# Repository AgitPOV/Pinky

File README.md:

Pinky
=====

Agit P.O.V. Pinky 2

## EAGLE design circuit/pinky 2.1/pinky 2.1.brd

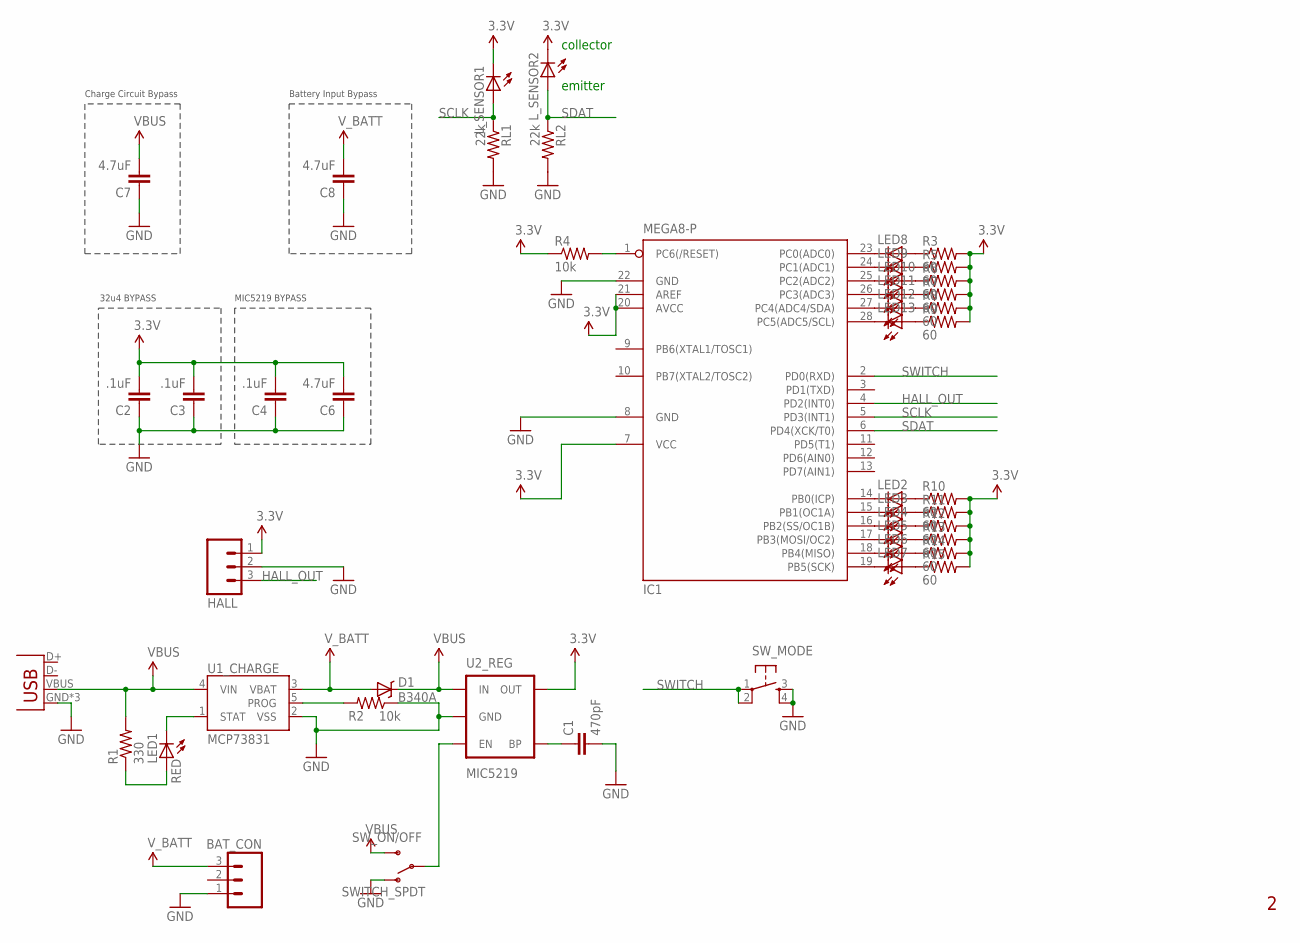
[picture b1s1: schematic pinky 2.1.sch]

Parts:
BAT_CON: M03PTH; 1X03
C1: 470pF; 1206
C2, C3, C4: .1uF; 1206
C6, C7, C8: 4.7uF; 1206
D1: B340A; SMA-DIODE
HALL: M03PTH; 1X03
IC1: MEGA8-P; DIL28-3
LED1: RED; LED-1206
LED2, LED3, LED4, LED5, LED6, LED7, LED8, LED9, LED10, LED11, LED12, LED13: LED1206; LED-1206
L_SENSOR1, L_SENSOR2: LED3MM
R1: 330; 1206
R2, R4: 10k; 1206
R3, R5, R6, R7, R8, R9, R10, R11, R12, R13, R14, R15: 60; 1206
RL1, RL2: 22k; 1206
SW_MODE: TAC_SWITCHPTH; TACTILE-PTH
SW_ON/OFF: SWITCH_SPDT; KPS-1290
U1_CHARGE: MCP73831; SOT23-5
U2_REG: MIC5219; SOT23-5
X1_USB_MICRO: USB-MICROB

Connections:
3.3V: C2.2, C3.2, C4.2, C6.2, HALL.1, IC1.7 (VCC), IC1.20 (AVCC), IC1.21 (AREF), L_SENSOR1.K (C), L_SENSOR2.K (C), R3.2, R4.1, R5.2, R6.2, R7.2, R8.2, R9.2, R10.2, R11.2, R12.2, R13.2, R14.2, R15.2, U2_REG.5 (OUT)
5V: C7.2, D1.C, R1.2, SW_ON/OFF.S, U1_CHARGE.4 (VIN), U2_REG.1 (IN), X1_USB_MICRO.VBUS
GND: BAT_CON.1, C1.2, C2.1, C3.1, C4.1, C6.1, C7.1, C8.1, HALL.2, IC1.8 (GND), IC1.22 (GND), R2.1, RL1.2, RL2.2, SW_MODE.3, SW_MODE.4, SW_ON/OFF.O, U1_CHARGE.2 (VSS), U2_REG.2 (GND), X1_USB_MICRO.GND, X1_USB_MICRO.MT1 (GND), X1_USB_MICRO.MT2 (GND)
HALL_OUT: HALL.3, IC1.4 (PD2(INT0))
unnamed: IC1.1 (PC6(/RESET)), R4.2
unnamed: SW_ON/OFF.P, U2_REG.3 (EN)
unnamed: LED1.A, R1.1
unnamed: LED1.C, U1_CHARGE.1 (STAT)
unnamed: IC1.14 (PB0(ICP)), LED2.C
unnamed: R2.2, U1_CHARGE.5 (PROG)
unnamed: IC1.15 (PB1(OC1A)), LED3.C
unnamed: C1.1, U2_REG.4 (BP)
unnamed: IC1.16 (PB2(SS/OC1B)), LED4.C
unnamed: IC1.17 (PB3(MOSI/OC2)), LED5.C
unnamed: IC1.18 (PB4(MISO)), LED6.C
unnamed: IC1.19 (PB5(SCK)), LED7.C
unnamed: IC1.23 (PC0(ADC0)), LED8.C
unnamed: IC1.24 (PC1(ADC1)), LED9.C
unnamed: IC1.25 (PC2(ADC2)), LED10.C
unnamed: IC1.26 (PC3(ADC3)), LED11.C
unnamed: IC1.27 (PC4(ADC4/SDA)), LED12.C
unnamed: IC1.28 (PC5(ADC5/SCL)), LED13.C
unnamed: LED8.A, R3.1
unnamed: LED9.A, R5.1
unnamed: LED10.A, R6.1
unnamed: LED11.A, R7.1
unnamed: LED12.A, R8.1
unnamed: LED13.A, R9.1
unnamed: LED2.A, R10.1
unnamed: LED3.A, R11.1
unnamed: LED4.A, R12.1
unnamed: LED5.A, R13.1
unnamed: LED6.A, R14.1
unnamed: LED7.A, R15.1
SCLK: IC1.5 (PD3(INT1)), L_SENSOR1.A, RL1.1
SDAT: IC1.6 (PD4(XCK/T0)), L_SENSOR2.A, RL2.1
SWITCH: IC1.2 (PD0(RXD)), SW_MODE.1, SW_MODE.2
V_BATT: BAT_CON.3, C8.2, D1.A, U1_CHARGE.3 (VBAT)

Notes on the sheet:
32u4 BYPASS
MIC5219 BYPASS
Charge Circuit Bypass
Battery Input Bypass
collector
emitter

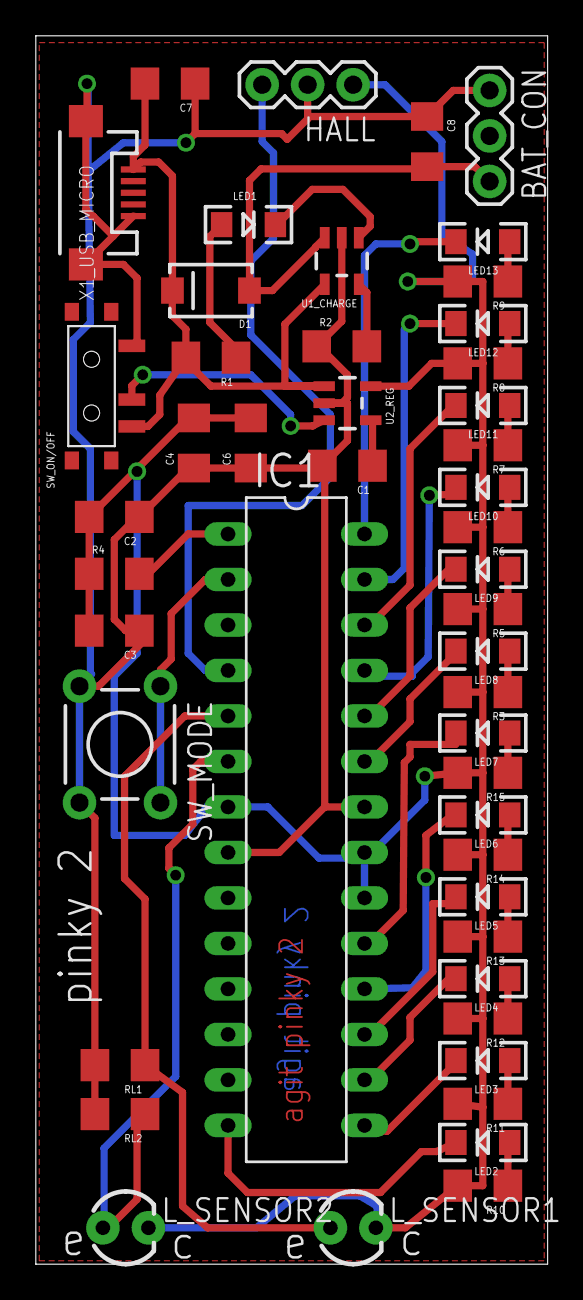
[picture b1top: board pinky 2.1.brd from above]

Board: 2 copper layers, 28.6 x 68.6 mm, 48 parts (0 on the bottom side), 38 nets.

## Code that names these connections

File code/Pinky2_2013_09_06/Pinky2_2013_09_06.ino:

#include <EEPROM.h>


// Use lillypad Arduino w/ atmega168

/*  
POV PIN CONFIGURTATION
Pinky mapping : ATMEGA168 : Arduino
LED0-LED5 : PB0-PB5 : 8,9,10,11,12,13
LED6-LED11 : PC0-PC5 : AN0, AN1, AN2, AN3, AN4, AN5
*/
unsigned char povPins[]={A5,A4,A3,A2,A1,A0,13,12,11,10,9,8};

/* 
POV INTERRUPT CONFIGURATION
what : interrupt : ATMEGA168 : Arduino
hall : 0 : PD2 : 2
*/
#define HALL_INTERRUPT 0
#define HALL_PIN 2

/*
MODES
*/
#define PLAYING 0
#define WRITING 1
#define WAITING 2
#define PLAYBACK 3
byte mode = PLAYING;



#define SWITCH_PIN 0
#define SCLK_PIN 3
#define SDAT_PIN 4

byte characterIndex = 0;
byte  bitIndex = 0;
char message[27]; 
byte messageLength;


unsigned long timeStamp;



void setup() {                

  pinMode(SWITCH_PIN,INPUT);
  digitalWrite(SWITCH_PIN,HIGH);
  
  
  for ( int i =0; i < 27; i++ ) message[i] = 0;
  
  povSetup();

  // A 3s fade out animation  
   timeStamp = millis();
   unsigned long microTimeStamp = micros();
  while ( (millis() - timeStamp) < 3000) {
    
      unsigned long lapsed = (micros() - microTimeStamp); // 0-3000000 
      
      unsigned long dim = lapsed / 300; // 0-10000
      unsigned long frame = lapsed % 10000; //0-10000
      
      if ( frame >= dim ) {
        for ( int i=0; i < 12 ; i++ ) digitalWrite( povPins[i],  LOW ); //ON
      } else {
        for ( int i=0; i < 12 ; i++ ) digitalWrite( povPins[i],  HIGH ); //OFF
      }
      
      
    
  }
  
  // Turn LEDS off
   for (unsigned char k=0;k<12;k++) {
    digitalWrite(povPins[k],HIGH);
  }


  // Check switch for mode
  // Go to WAITING to WRITING mode if switch is pressed  
  if ( digitalRead(SWITCH_PIN) == LOW ) mode = WAITING;


  // SETUP MODE


  if ( mode == PLAYING ) {

    readMessage();
   


  }  else { // mode == WRITING OR WAITING

    pinMode(SCLK_PIN,INPUT);
    pinMode(SDAT_PIN,INPUT);

  }
  
  
  timeStamp = millis();

}

// the loop routine runs over and over again forever:
void loop() {

  if ( mode == PLAYING ) {

     povWaitAndDisplay();
    //povDisplay();

  } 
  else if ( mode == WAITING) {
    
      
  
    unsigned long lighted = ((millis() - timeStamp) / 125) % 12;
    for ( int i=0; i < 12 ; i++ ) {
      digitalWrite( povPins[i],  (lighted != i ));
    }
    
    
    if ( digitalRead(SWITCH_PIN) == HIGH &&  digitalRead(SCLK_PIN) == LOW && digitalRead(SDAT_PIN) == LOW ) { // Button released and nothing is detected
        
        for ( int i=0; i < 12 ; i++ ) {
          digitalWrite( povPins[i],  HIGH);
        }
        
        
        //while( digitalRead(SCLK_PIN) == HIGH || digitalRead(SDAT_PIN) == HIGH) ; // Wait till nothing is detected
        timeStamp = millis();
        
        attachInterrupt(1,SCLKInterrupt, FALLING);
        mode = WRITING;
         
    }
    
    
  } else if ( mode == PLAYBACK) {
    
    povDisplay();
    
    
  } else { // mode == WRITING
  
   digitalWrite( povPins[0],  (millis() / 125) % 2 );
      digitalWrite(povPins[1], !digitalRead(SCLK_PIN) );
   
   digitalWrite(povPins[2], !digitalRead(SDAT_PIN) );
    
  }
}



void SCLKInterrupt() {
  
  if ( millis() - timeStamp > 500 ) {
  int sdatState = digitalRead(SDAT_PIN);
  

  
  message[characterIndex] = message[characterIndex] | ( sdatState << bitIndex );
  bitIndex++;
  
  if ( bitIndex == 8 ) {
    bitIndex=0;


    if ( characterIndex == 26 ) {
      message[characterIndex] = 0;     
    }

    if ( message[characterIndex] == 0 )  {
      saveMessage();
    }
    else {
      characterIndex=characterIndex+1; 
    }


  }
  }

}

void saveMessage() {
  detachInterrupt(1);

  messageLength = characterIndex + 1;


  for ( byte i = 0; i < messageLength; i++ ) {
    EEPROM.write(i,message[i]);
    if ( message[i] == 0 ) break;
  }

  mode = PLAYBACK;

  povSetMessage(&message[0]);

}

void readMessage() {
  boolean ok = true;

  for ( byte i = 0; i < 26; i++ ) {
    byte b = EEPROM.read(i);
    if ( b > 127 ) {
      ok = false;
      break;
    }
    message[i] = b;
    if ( b == 0 ) {
      if ( i == 0 ) ok = false;
      break;
    }
  }
  message[26] = 0; // failsafe
  
  if ( ok ) {
     povSetMessage(&message[0]);
  } else {
     povSetMessage("PINKY");
  }
   
}

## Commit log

2014-09-23 No idea

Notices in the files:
parts and their libraries:
SparkFun-PowerIC: Licensing: CC v3.0 Share-Alike You are welcome to use this library for commercial purposes.
SparkFun-Aesthetics: Released under the Creative Commons
SparkFun-Aesthetics: http://creativecommons.org/licenses/by-sa/3.0
